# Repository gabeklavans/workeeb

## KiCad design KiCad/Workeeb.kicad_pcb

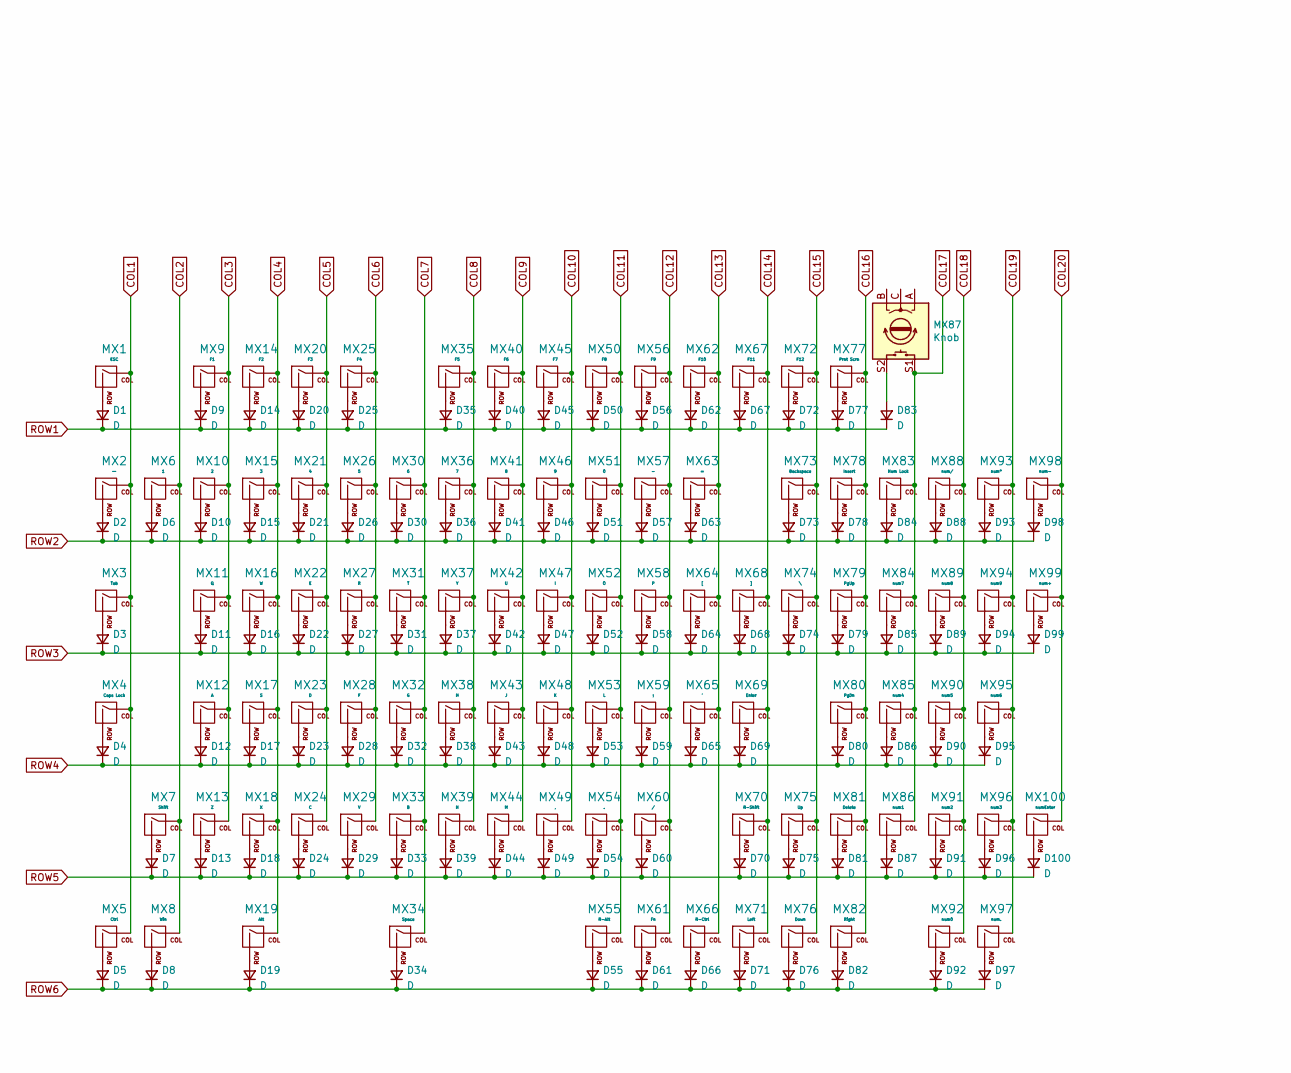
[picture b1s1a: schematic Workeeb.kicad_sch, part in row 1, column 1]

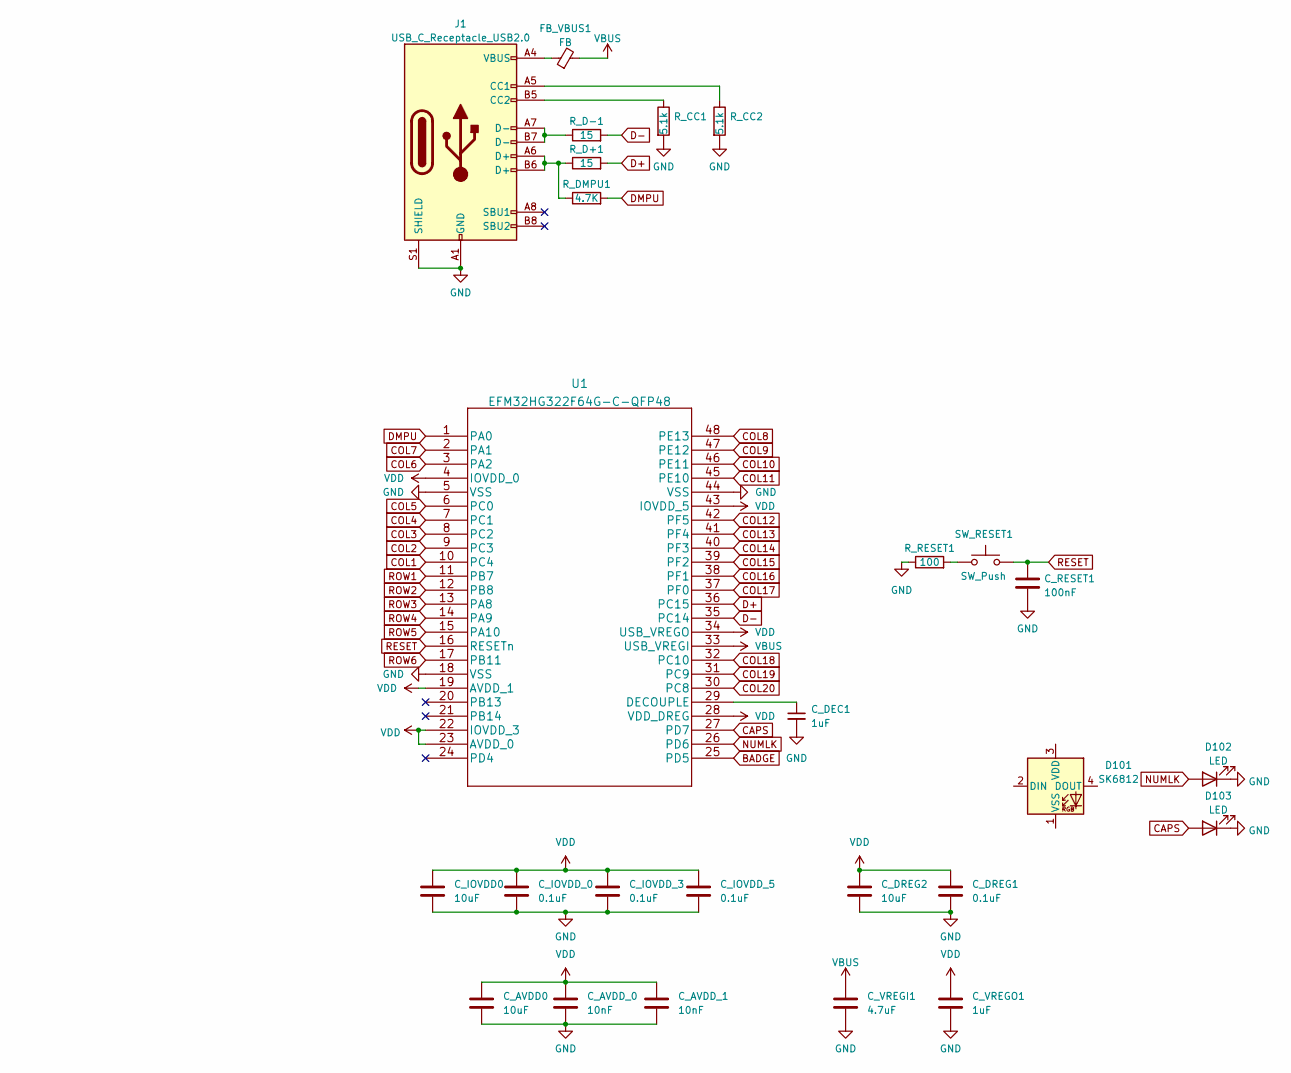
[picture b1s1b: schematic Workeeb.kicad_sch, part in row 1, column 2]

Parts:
C_AVDD0: 10uF; C_0402_1005Metric
C_AVDD_0, C_AVDD_1: 10nF; C_0402_1005Metric
C_DEC1: 1uF; C_0402_1005Metric
C_DREG1: 0.1uF; C_0402_1005Metric
C_DREG2: 10uF; C_0402_1005Metric
C_IOVDD0: 10uF; C_0402_1005Metric
C_IOVDD_0, C_IOVDD_3, C_IOVDD_5: 0.1uF; C_0402_1005Metric
C_RESET1: 100nF; C_0402_1005Metric
C_VREGI1: 4.7uF; C_0402_1005Metric
C_VREGO1: 1uF; C_0402_1005Metric
D1, D2, D3, D4, D5, D6, D7, D8, D9, D10, D11, D12, D13, D14, D15, D16, D17, D18, D19, D20, D21, D22, D23, D24, D25, D26, D27, D28, D29, D30, D31, D32, D33, D34, D35, D36, D37, D38, D39, D40, D41, D42, D43, D44, D45, D46, D47, D48, D49, D50, D51, D52, D53, D54, D55, D56, D57, D58, D59, D60, D61, D62, D63, D64, D65, D66, D67, D68, D69, D70, D71, D72, D73, D74, D75, D76, D77, D78, D79, D80, D81, D82, D83, D84, D85, D86, D87, D88, D89, D90, D91, D92, D93, D94, D95, D96, D97, D98, D99, D100: D; D_SOD-123
D101: SK6812; LED_SK6812_PLCC4_5.0x5.0mm_P3.2mm
D102, D103: LED; LED_1206_3216Metric_Pad1.42x1.75mm_HandSolder
FB_VBUS1: FB; L_0805_2012Metric
J1: USB_C_Receptacle_USB2.0; USB_C_Receptacle_GCT_USB4085
MX1: ESC; MXOnly-1U-NoLED
MX2: ~~; MXOnly-1U-NoLED
MX3: Tab; MXOnly-1.5U-NoLED
MX4: Caps Lock; MXOnly-1.75U-NoLED
MX5: Ctrl; MXOnly-1.25U-NoLED
MX6: 1; MXOnly-1U-NoLED
MX7: Shift; MXOnly-2.25U-NoLED
MX8: Win; MXOnly-1.25U-NoLED
MX9: F1; MXOnly-1U-NoLED
MX10: 2; MXOnly-1U-NoLED
MX11: Q; MXOnly-1U-NoLED
MX12: A; MXOnly-1U-NoLED
MX13: Z; MXOnly-1U-NoLED
MX14: F2; MXOnly-1U-NoLED
MX15: 3; MXOnly-1U-NoLED
MX16: W; MXOnly-1U-NoLED
MX17: S; MXOnly-1U-NoLED
MX18: X; MXOnly-1U-NoLED
MX19: Alt; MXOnly-1.25U-NoLED
MX20: F3; MXOnly-1U-NoLED
MX21: 4; MXOnly-1U-NoLED
MX22: E; MXOnly-1U-NoLED
MX23: D; MXOnly-1U-NoLED
MX24: C; MXOnly-1U-NoLED
MX25: F4; MXOnly-1U-NoLED
MX26: 5; MXOnly-1U-NoLED
MX27: R; MXOnly-1U-NoLED
MX28: F; MXOnly-1U-NoLED
MX29: V; MXOnly-1U-NoLED
MX30: 6; MXOnly-1U-NoLED
MX31: T; MXOnly-1U-NoLED
MX32: G; MXOnly-1U-NoLED
MX33: B; MXOnly-1U-NoLED
MX34: Space; MXOnly-6.25U-NoLED
MX35: F5; MXOnly-1U-NoLED
MX36: 7; MXOnly-1U-NoLED
MX37: Y; MXOnly-1U-NoLED
MX38: H; MXOnly-1U-NoLED
MX39: N; MXOnly-1U-NoLED
MX40: F6; MXOnly-1U-NoLED
MX41: 8; MXOnly-1U-NoLED
MX42: U; MXOnly-1U-NoLED
MX43: J; MXOnly-1U-NoLED
MX44: M; MXOnly-1U-NoLED
MX45: F7; MXOnly-1U-NoLED
MX46: 9; MXOnly-1U-NoLED
MX47: I; MXOnly-1U-NoLED
MX48: K; MXOnly-1U-NoLED
MX49: ,; MXOnly-1U-NoLED
MX50: F8; MXOnly-1U-NoLED
MX51: 0; MXOnly-1U-NoLED
MX52: O; MXOnly-1U-NoLED
MX53: L; MXOnly-1U-NoLED
MX54: .; MXOnly-1U-NoLED
MX55: R-Alt; MXOnly-1U-NoLED
MX56: F9; MXOnly-1U-NoLED
MX57: -; MXOnly-1U-NoLED
MX58: P; MXOnly-1U-NoLED
MX59: ;; MXOnly-1U-NoLED
MX60: /; MXOnly-1U-NoLED
MX61: Fn; MXOnly-1U-NoLED
MX62: F10; MXOnly-1U-NoLED
MX63: =; MXOnly-1U-NoLED
MX64: [; MXOnly-1U-NoLED
MX65: '; MXOnly-1U-NoLED
MX66: R-Ctrl; MXOnly-1U-NoLED
MX67: F11; MXOnly-1U-NoLED
MX68: ]; MXOnly-1U-NoLED
MX69: Enter; MXOnly-2.25U-NoLED
MX70: R-Shift; MXOnly-1.75U-NoLED
MX71: Left; MXOnly-1U-NoLED
MX72: F12; MXOnly-1U-NoLED
MX73: Backspace; MXOnly-2U-NoLED
MX74: \; MXOnly-1.5U-NoLED
MX75: Up; MXOnly-1U-NoLED
MX76: Down; MXOnly-1U-NoLED
MX77: Prnt Scrn; MXOnly-1U-NoLED
MX78: Insert; MXOnly-1U-NoLED
MX79: PgUp; MXOnly-1U-NoLED
MX80: PgDn; MXOnly-1U-NoLED
MX81: Delete; MXOnly-1U-NoLED
MX82: Right; MXOnly-1U-NoLED
MX83: Num Lock; MXOnly-1U-NoLED
MX84: num7; MXOnly-1U-NoLED
MX85: num4; MXOnly-1U-NoLED
MX86: num1; MXOnly-1U-NoLED
MX87: Knob; RotaryEncoder_Alps_EC12E-Switch_Vertical_H20mm
MX88: num/; MXOnly-1U-NoLED
MX89: num8; MXOnly-1U-NoLED
MX90: num5; MXOnly-1U-NoLED
MX91: num2; MXOnly-1U-NoLED
MX92: num0; MXOnly-2U-NoLED
MX93: num*; MXOnly-1U-NoLED
MX94: num9; MXOnly-1U-NoLED
MX95: num6; MXOnly-1U-NoLED
MX96: num3; MXOnly-1U-NoLED
MX97: num.; MXOnly-1U-NoLED
MX98: num-; MXOnly-1U-NoLED
MX99: num+; MXOnly-2U-VerticalStabilizers-NoLED
MX100: numEnter; MXOnly-2U-VerticalStabilizers-NoLED
R_CC1, R_CC2: 5.1k; R_0805_2012Metric
R_D+1: 15; R_0805_2012Metric
R_D-1: 15; R_0805_2012Metric
R_DMPU1: 4.7K; R_0805_2012Metric
R_RESET1: 100; R_0805_2012Metric
SW_RESET1: SW_Push; PushButton_6x6mm_TH_Pretty
U1: EFM32HG322F64G-C-QFP48

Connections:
BADGE: U1.25 (PD5)
CAPS: D103.2 (A), U1.27 (PD7)
COL1: MX1.1 (COL), MX2.1 (COL), MX3.1 (COL), MX4.1 (COL), MX5.1 (COL), U1.10 (PC4)
COL2: MX6.1 (COL), MX7.1 (COL), MX8.1 (COL), U1.9 (PC3)
COL3: MX9.1 (COL), MX10.1 (COL), MX11.1 (COL), MX12.1 (COL), MX13.1 (COL), U1.8 (PC2)
COL4: MX14.1 (COL), MX15.1 (COL), MX16.1 (COL), MX17.1 (COL), MX18.1 (COL), MX19.1 (COL), U1.7 (PC1)
COL5: MX20.1 (COL), MX21.1 (COL), MX22.1 (COL), MX23.1 (COL), MX24.1 (COL), U1.6 (PC0)
COL6: MX25.1 (COL), MX26.1 (COL), MX27.1 (COL), MX28.1 (COL), MX29.1 (COL), U1.3 (PA2)
COL7: MX30.1 (COL), MX31.1 (COL), MX32.1 (COL), MX33.1 (COL), MX34.1 (COL), U1.2 (PA1)
COL8: MX35.1 (COL), MX36.1 (COL), MX37.1 (COL), MX38.1 (COL), MX39.1 (COL), U1.48 (PE13)
COL9: MX40.1 (COL), MX41.1 (COL), MX42.1 (COL), MX43.1 (COL), MX44.1 (COL), U1.47 (PE12)
COL10: MX45.1 (COL), MX46.1 (COL), MX47.1 (COL), MX48.1 (COL), MX49.1 (COL), U1.46 (PE11)
COL11: MX50.1 (COL), MX51.1 (COL), MX52.1 (COL), MX53.1 (COL), MX54.1 (COL), MX55.1 (COL), U1.45 (PE10)
COL12: MX56.1 (COL), MX57.1 (COL), MX58.1 (COL), MX59.1 (COL), MX60.1 (COL), MX61.1 (COL), U1.42 (PF5)
COL13: MX62.1 (COL), MX63.1 (COL), MX64.1 (COL), MX65.1 (COL), MX66.1 (COL), U1.41 (PF4)
COL14: MX67.1 (COL), MX68.1 (COL), MX69.1 (COL), MX70.1 (COL), MX71.1 (COL), U1.40 (PF3)
COL15: MX72.1 (COL), MX73.1 (COL), MX74.1 (COL), MX75.1 (COL), MX76.1 (COL), U1.39 (PF2)
COL16: MX77.1 (COL), MX78.1 (COL), MX79.1 (COL), MX80.1 (COL), MX81.1 (COL), MX82.1 (COL), U1.38 (PF1)
COL17: MX83.1 (COL), MX84.1 (COL), MX85.1 (COL), MX86.1 (COL), MX87.S1, U1.37 (PF0)
COL18: MX88.1 (COL), MX89.1 (COL), MX90.1 (COL), MX91.1 (COL), MX92.1 (COL), U1.32 (PC10)
COL19: MX93.1 (COL), MX94.1 (COL), MX95.1 (COL), MX96.1 (COL), MX97.1 (COL), U1.31 (PC9)
COL20: MX98.1 (COL), MX99.1 (COL), MX100.1 (COL), U1.30 (PC8)
D+: R_D+1.2, U1.36 (PC15)
D-: R_D-1.2, U1.35 (PC14)
DMPU: R_DMPU1.2, U1.1 (PA0)
GND: C_AVDD0.2, C_AVDD_0.2, C_AVDD_1.2, C_DEC1.2, C_DREG1.2, C_DREG2.2, C_IOVDD0.2, C_IOVDD_0.2, C_IOVDD_3.2, C_IOVDD_5.2, C_RESET1.2, C_VREGI1.2, C_VREGO1.2, D102.1 (K), D103.1 (K), J1.A1 (GND), J1.A12 (GND), J1.B1 (GND), J1.B12 (GND), J1.S1 (SHIELD), R_CC1.2, R_CC2.2, R_RESET1.1, U1.5 (VSS), U1.18 (VSS), U1.44 (VSS)
NUMLK: D102.2 (A), U1.26 (PD6)
unnamed: C_DEC1.1, U1.29 (DECOUPLE)
unnamed: D1.2 (A), MX1.2 (ROW)
unnamed: D2.2 (A), MX2.2 (ROW)
unnamed: D3.2 (A), MX3.2 (ROW)
unnamed: D4.2 (A), MX4.2 (ROW)
unnamed: D5.2 (A), MX5.2 (ROW)
unnamed: D6.2 (A), MX6.2 (ROW)
unnamed: D7.2 (A), MX7.2 (ROW)
unnamed: D8.2 (A), MX8.2 (ROW)
unnamed: D9.2 (A), MX9.2 (ROW)
unnamed: D10.2 (A), MX10.2 (ROW)
unnamed: D11.2 (A), MX11.2 (ROW)
unnamed: D12.2 (A), MX12.2 (ROW)
unnamed: D13.2 (A), MX13.2 (ROW)
unnamed: D14.2 (A), MX14.2 (ROW)
unnamed: D15.2 (A), MX15.2 (ROW)
unnamed: D16.2 (A), MX16.2 (ROW)
unnamed: D17.2 (A), MX17.2 (ROW)
unnamed: D18.2 (A), MX18.2 (ROW)
unnamed: D19.2 (A), MX19.2 (ROW)
unnamed: D20.2 (A), MX20.2 (ROW)
unnamed: D21.2 (A), MX21.2 (ROW)
unnamed: D22.2 (A), MX22.2 (ROW)
unnamed: D23.2 (A), MX23.2 (ROW)
unnamed: D24.2 (A), MX24.2 (ROW)
unnamed: D25.2 (A), MX25.2 (ROW)
unnamed: D26.2 (A), MX26.2 (ROW)
unnamed: D27.2 (A), MX27.2 (ROW)
unnamed: D28.2 (A), MX28.2 (ROW)
unnamed: D29.2 (A), MX29.2 (ROW)
unnamed: D30.2 (A), MX30.2 (ROW)
unnamed: D31.2 (A), MX31.2 (ROW)
unnamed: D32.2 (A), MX32.2 (ROW)
unnamed: D33.2 (A), MX33.2 (ROW)
unnamed: D34.2 (A), MX34.2 (ROW)
unnamed: D35.2 (A), MX35.2 (ROW)
unnamed: D36.2 (A), MX36.2 (ROW)
unnamed: D37.2 (A), MX37.2 (ROW)
unnamed: D38.2 (A), MX38.2 (ROW)
unnamed: D39.2 (A), MX39.2 (ROW)
unnamed: D40.2 (A), MX40.2 (ROW)
unnamed: D41.2 (A), MX41.2 (ROW)
unnamed: D42.2 (A), MX42.2 (ROW)
unnamed: D43.2 (A), MX43.2 (ROW)
unnamed: D44.2 (A), MX44.2 (ROW)
unnamed: D45.2 (A), MX45.2 (ROW)
unnamed: D46.2 (A), MX46.2 (ROW)
unnamed: D47.2 (A), MX47.2 (ROW)
unnamed: D48.2 (A), MX48.2 (ROW)
unnamed: D49.2 (A), MX49.2 (ROW)
unnamed: D50.2 (A), MX50.2 (ROW)
unnamed: D51.2 (A), MX51.2 (ROW)
unnamed: D52.2 (A), MX52.2 (ROW)
unnamed: D53.2 (A), MX53.2 (ROW)
unnamed: D54.2 (A), MX54.2 (ROW)
unnamed: D55.2 (A), MX55.2 (ROW)
unnamed: D56.2 (A), MX56.2 (ROW)
unnamed: D57.2 (A), MX57.2 (ROW)
unnamed: D58.2 (A), MX58.2 (ROW)
unnamed: D59.2 (A), MX59.2 (ROW)
unnamed: D60.2 (A), MX60.2 (ROW)
unnamed: D61.2 (A), MX61.2 (ROW)
unnamed: D62.2 (A), MX62.2 (ROW)
unnamed: D63.2 (A), MX63.2 (ROW)
unnamed: D64.2 (A), MX64.2 (ROW)
unnamed: D65.2 (A), MX65.2 (ROW)
unnamed: D66.2 (A), MX66.2 (ROW)
unnamed: D67.2 (A), MX67.2 (ROW)
unnamed: D68.2 (A), MX68.2 (ROW)
unnamed: D69.2 (A), MX69.2 (ROW)
unnamed: D70.2 (A), MX70.2 (ROW)
unnamed: D71.2 (A), MX71.2 (ROW)
unnamed: D72.2 (A), MX72.2 (ROW)
unnamed: D73.2 (A), MX73.2 (ROW)
unnamed: D74.2 (A), MX74.2 (ROW)
unnamed: D75.2 (A), MX75.2 (ROW)
unnamed: D76.2 (A), MX76.2 (ROW)
unnamed: D77.2 (A), MX77.2 (ROW)
unnamed: D78.2 (A), MX78.2 (ROW)
unnamed: D79.2 (A), MX79.2 (ROW)
unnamed: D80.2 (A), MX80.2 (ROW)
unnamed: D81.2 (A), MX81.2 (ROW)
unnamed: D82.2 (A), MX82.2 (ROW)
unnamed: D83.2 (A), MX87.S2
unnamed: D84.2 (A), MX83.2 (ROW)
unnamed: D85.2 (A), MX84.2 (ROW)
unnamed: D86.2 (A), MX85.2 (ROW)
unnamed: D87.2 (A), MX86.2 (ROW)
unnamed: D88.2 (A), MX88.2 (ROW)
unnamed: D89.2 (A), MX89.2 (ROW)
unnamed: D90.2 (A), MX90.2 (ROW)
unnamed: D91.2 (A), MX91.2 (ROW)
unnamed: D92.2 (A), MX92.2 (ROW)
unnamed: D93.2 (A), MX93.2 (ROW)
unnamed: D94.2 (A), MX94.2 (ROW)
unnamed: D95.2 (A), MX95.2 (ROW)
unnamed: D96.2 (A), MX96.2 (ROW)
unnamed: D97.2 (A), MX97.2 (ROW)
unnamed: D98.2 (A), MX98.2 (ROW)
unnamed: D99.2 (A), MX99.2 (ROW)
unnamed: D100.2 (A), MX100.2 (ROW)
unnamed: FB_VBUS1.1, J1.A4 (VBUS), J1.A9 (VBUS), J1.B4 (VBUS), J1.B9 (VBUS)
unnamed: J1.A5 (CC1), R_CC2.1
unnamed: J1.A6 (D+), J1.B6 (D+), R_D+1.1, R_DMPU1.1
unnamed: J1.A7 (D-), J1.B7 (D-), R_D-1.1
unnamed: J1.B5 (CC2), R_CC1.1
unnamed: R_RESET1.2, SW_RESET1.1
RESET: C_RESET1.1, SW_RESET1.2, U1.16 (RESETn)
ROW1: D1.1 (K), D9.1 (K), D14.1 (K), D20.1 (K), D25.1 (K), D35.1 (K), D40.1 (K), D45.1 (K), D50.1 (K), D56.1 (K), D62.1 (K), D67.1 (K), D72.1 (K), D77.1 (K), D83.1 (K), U1.11 (PB7)
ROW2: D2.1 (K), D6.1 (K), D10.1 (K), D15.1 (K), D21.1 (K), D26.1 (K), D30.1 (K), D36.1 (K), D41.1 (K), D46.1 (K), D51.1 (K), D57.1 (K), D63.1 (K), D73.1 (K), D78.1 (K), D84.1 (K), D88.1 (K), D93.1 (K), D98.1 (K), U1.12 (PB8)
ROW3: D3.1 (K), D11.1 (K), D16.1 (K), D22.1 (K), D27.1 (K), D31.1 (K), D37.1 (K), D42.1 (K), D47.1 (K), D52.1 (K), D58.1 (K), D64.1 (K), D68.1 (K), D74.1 (K), D79.1 (K), D85.1 (K), D89.1 (K), D94.1 (K), D99.1 (K), U1.13 (PA8)
ROW4: D4.1 (K), D12.1 (K), D17.1 (K), D23.1 (K), D28.1 (K), D32.1 (K), D38.1 (K), D43.1 (K), D48.1 (K), D53.1 (K), D59.1 (K), D65.1 (K), D69.1 (K), D80.1 (K), D86.1 (K), D90.1 (K), D95.1 (K), U1.14 (PA9)
ROW5: D7.1 (K), D13.1 (K), D18.1 (K), D24.1 (K), D29.1 (K), D33.1 (K), D39.1 (K), D44.1 (K), D49.1 (K), D54.1 (K), D60.1 (K), D70.1 (K), D75.1 (K), D81.1 (K), D87.1 (K), D91.1 (K), D96.1 (K), D100.1 (K), U1.15 (PA10)
ROW6: D5.1 (K), D8.1 (K), D19.1 (K), D34.1 (K), D55.1 (K), D61.1 (K), D66.1 (K), D71.1 (K), D76.1 (K), D82.1 (K), D92.1 (K), D97.1 (K), U1.17 (PB11)
VBUS: C_VREGI1.1, FB_VBUS1.2, U1.33 (USB_VREGI)
VDD: C_AVDD0.1, C_AVDD_0.1, C_AVDD_1.1, C_DREG1.1, C_DREG2.1, C_IOVDD0.1, C_IOVDD_0.1, C_IOVDD_3.1, C_IOVDD_5.1, C_VREGO1.1, U1.4 (IOVDD_0), U1.19 (AVDD_1), U1.22 (IOVDD_3), U1.23 (AVDD_0), U1.28 (VDD_DREG), U1.34 (USB_VREGO), U1.43 (IOVDD_5)

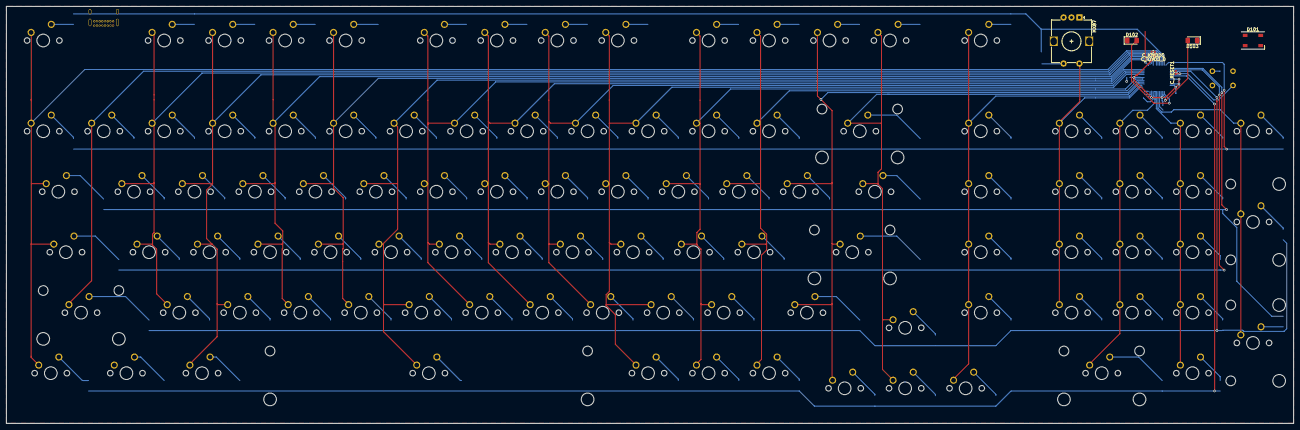
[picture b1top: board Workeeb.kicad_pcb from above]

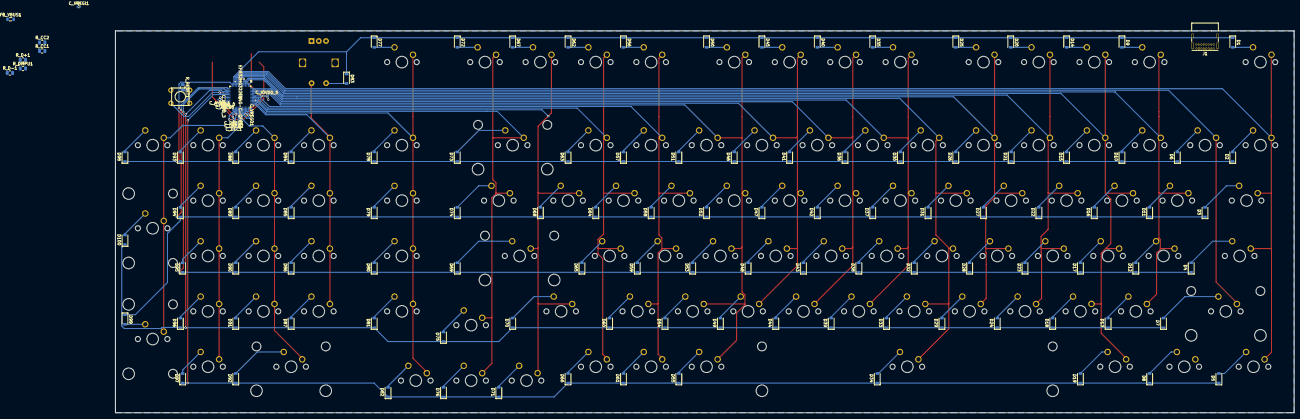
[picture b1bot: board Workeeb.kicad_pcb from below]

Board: 2 copper layers, 405.4 x 131.3 mm, 226 parts (120 on the bottom side), 142 nets.

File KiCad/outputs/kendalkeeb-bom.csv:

Comment,Designator,Footprint
,MX2,MXOnly-1U-NoLED
,MX3,MXOnly-1.5U-NoLED
,MX4,MXOnly-1.75U-NoLED
,MX5,MXOnly-1.25U-NoLED
,MX7,MXOnly-2.25U-NoLED
,MX8,MXOnly-1.25U-NoLED
,MX9,MXOnly-1U-NoLED
,MX10,MXOnly-1U-NoLED
,MX11,MXOnly-1U-NoLED
,MX12,MXOnly-1U-NoLED
,MX13,MXOnly-1U-NoLED
,MX14,MXOnly-1U-NoLED
,MX15,MXOnly-1U-NoLED
,MX16,MXOnly-1U-NoLED
,MX17,MXOnly-1U-NoLED
,MX18,MXOnly-1U-NoLED
,MX19,MXOnly-1.25U-NoLED
,MX20,MXOnly-1U-NoLED
,MX21,MXOnly-1U-NoLED
,MX22,MXOnly-1U-NoLED
,MX23,MXOnly-1U-NoLED
,MX24,MXOnly-1U-NoLED
,MX25,MXOnly-1U-NoLED
,MX26,MXOnly-1U-NoLED
,MX27,MXOnly-1U-NoLED
,MX28,MXOnly-1U-NoLED
,MX29,MXOnly-1U-NoLED
,MX30,MXOnly-1U-NoLED
,MX31,MXOnly-1U-NoLED
,MX32,MXOnly-1U-NoLED
,MX33,MXOnly-1U-NoLED
,MX34,MXOnly-6.25U-NoLED
,MX35,MXOnly-1U-NoLED
,MX36,MXOnly-1U-NoLED
,MX37,MXOnly-1U-NoLED
,MX38,MXOnly-1U-NoLED
,MX39,MXOnly-1U-NoLED
,MX40,MXOnly-1U-NoLED
,MX41,MXOnly-1U-NoLED
,MX42,MXOnly-1U-NoLED
,MX43,MXOnly-1U-NoLED
,MX44,MXOnly-1U-NoLED
,MX45,MXOnly-1U-NoLED
,MX46,MXOnly-1U-NoLED
,MX47,MXOnly-1U-NoLED
,MX48,MXOnly-1U-NoLED
,MX49,MXOnly-1U-NoLED
,MX50,MXOnly-1U-NoLED
,MX51,MXOnly-1U-NoLED
,MX52,MXOnly-1U-NoLED
,MX53,MXOnly-1U-NoLED
,MX54,MXOnly-1U-NoLED
,MX55,MXOnly-1U-NoLED
,MX56,MXOnly-1U-NoLED
,MX57,MXOnly-1U-NoLED
,MX58,MXOnly-1U-NoLED
,MX59,MXOnly-1U-NoLED
,MX60,MXOnly-1U-NoLED
,MX61,MXOnly-1U-NoLED
,MX62,MXOnly-1U-NoLED
,MX63,MXOnly-1U-NoLED
,MX64,MXOnly-1U-NoLED
,MX65,MXOnly-1U-NoLED
,MX66,MXOnly-1U-NoLED
,MX67,MXOnly-1U-NoLED
,MX68,MXOnly-1U-NoLED
,MX69,MXOnly-2.25U-NoLED
,MX70,MXOnly-1.75U-NoLED
,MX71,MXOnly-1U-NoLED
,MX73,MXOnly-2U-NoLED
,MX74,MXOnly-1.5U-NoLED
,MX75,MXOnly-1U-NoLED
,MX76,MXOnly-1U-NoLED
,MX77,MXOnly-1U-NoLED
,MX78,MXOnly-1U-NoLED
,MX79,MXOnly-1U-NoLED
,MX80,MXOnly-1U-NoLED
,MX81,MXOnly-1U-NoLED
,MX82,MXOnly-1U-NoLED
,MX83,MXOnly-1U-NoLED
,MX84,MXOnly-1U-NoLED
,MX85,MXOnly-1U-NoLED
,MX86,MXOnly-1U-NoLED
,MX87,RotaryEncoder_Alps_EC12E-Switch_Vertical_H20mm
,MX89,MXOnly-1U-NoLED
,MX90,MXOnly-1U-NoLED
,MX91,MXOnly-1U-NoLED
,MX92,MXOnly-2U-NoLED
,MX93,MXOnly-1U-NoLED
,MX95,MXOnly-1U-NoLED
,MX96,MXOnly-1U-NoLED
,MX97,MXOnly-1U-NoLED
,MX98,MXOnly-1U-NoLED
,MX99,MXOnly-2U-VerticalStabilizers-NoLED
,MX1,MXOnly-1U-NoLED
,MX6,MXOnly-1U-NoLED
,MX72,MXOnly-1U-NoLED
,D101,LED_SK6812_PLCC4_5.0x5.0mm_P3.2mm
10,"R_CAPS1,R_NUMLK1",R_0805_2012Metric
,MX94,MXOnly-1U-NoLED
100nF,C_RESET1,C_0402_1005Metric
,MX100,MXOnly-2U-VerticalStabilizers-NoLED
,MX88,MXOnly-1U-NoLED
,"D102,D103",LED_1206_3216Metric_Pad1.42x1.75mm_HandSolder
10uF,"C_IOVDD0,C_AVDD0,C_DREG2",C_0402_1005Metric
0.1uf,"C_IOVDD_0,C_IOVDD_5,C_DREG1,C_IOVDD_3",C_0402_1005Metric
500,R_BADGE1,R_0805_2012Metric
100,"D5,D9,D74,D64,D29,D60,D75,D70,D65,D83,D47,D93,D23,D87,D27,D8,D13,D16,D45,D36,D67,D54,D71,D73,D28,D80,D98,D18,D32,D43,D46,D78,D38,D12,D11,D81,D37,D66,D30,D86,D39,D40,D59,D42,D44,D52,D69,D48,D10,D51,D3,D7,D2,D24,D58,D41,D34,D17,D96,D97,D50,D20,D14,D77,D25,D49,D89,D19,D94,D95,D76,D72,D61,D85,D82,D26,D1,D15,D57,D6,D53,D55,D63,D31,D100,D56,D33,D92,D91,D79,D99,D62,D22,D90,D68,D84,D35,D4,D21,D88",D_SOD-123
1uf,"C_VREGO1,C_DEC1",C_0402_1005Metric
10nf,"C_AVDD_0,C_AVDD_1",C_0402_1005Metric
5.1k,"R_CC2,R_CC1",R_0805_2012Metric
,U1,EFM32HG322F64G-C-QFP48
15,"R_D-1,R_D+1",R_0805_2012Metric
,FB_VBUS1,L_0805_2012Metric
,J1,USB_C_Receptacle_GCT_USB4085
4.7uF,C_VREGI1,C_0402_1005Metric
100,R_RESET1,R_0805_2012Metric
4.7k,R_DMPU1,R_0805_2012Metric
,SW_RESET1,PushButton_6x6mm_TH_Pretty

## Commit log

2021-11-26 initty committy
2021-11-26 begone, store
2021-11-26 ignstore
2022-02-07 Added mx alps hybrid footprint as submodule
2022-02-07 Add some backup files and more MX labels
2022-02-07 Finish setting values of switches, start PCB placement
2022-02-08 Add chosen MCU lib and connect a little
2022-02-09 Place some things and rename some stuff
2022-02-19 Upgrade to KiCad6
    Finish placing switches in PCB
2022-02-19 ignore backups folder
2022-02-19 Finish duplex matrix for reducing pin count
    Also add Keebio repos for Elite-C
2022-02-19 Match up the diodes and Elite-C footprint
2022-06-10 Add EFM32HG322F64G-C-QFP48 symbol and footprint
2022-06-11 Begin lengthy process of hooking up switches/designing power circuitry
2022-06-12 start bad version of decoupling cap schema
2022-06-13 Start proper power routing
2022-06-13 Clean up MCU pwr connections
    Start laying out decoupling caps
2022-06-15 Finish up schematic first draft
    Mess around a bit with PCB
2022-06-28 Place all diodes and fix switch annotations
2022-06-28 Connect up row diodes
2022-07-20 Route all left-side cols to MCU area
2022-07-20 Reorder row/cols to match physical layout of routes better
2022-08-02 Moved diodes into new place for better col routing
2022-08-02 Removed old vias
2022-08-02 Start to do power routing
2022-08-09 Better cap names, start placing decoupling caps
2022-08-10 Work towards getting decoupling caps and col routes in place
2022-08-17 Connect up a bunch more stuff and set ground plane zone
2022-08-17 Draft finish PCB
2022-08-17 Add resistors for white LEDs
2022-08-18 smallify some text
2022-08-18 finish up DRC warns/errs
2022-08-21 Add a bunch of output files
    Add cute lil graphics (or their placeholders) to the bottom of the board
2022-08-21 Placeholder graphic
2022-08-21 more descriptive silkscreen
2022-08-21 Updated/better outputs organization
2022-09-09 Unified pos and better bom
2022-09-09 Expand edges by ~6mm

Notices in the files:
parts and their libraries:
Copyright 2021 Accelerated Designs. All rights reserved.
